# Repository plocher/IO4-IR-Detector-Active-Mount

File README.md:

# IO4-IR-Detector-Active-Mount
## License: CERN Open Hardware Licence v1.2

Mounting adapter for active IR detector remote sensor

  Designed for the Rolm RPR-220-photoreflector or equivalent IR transmitter/Detector

  * Drill a hole under the track / between the rails for the detector sensor 
  * Measure the roadbed depth and solder the sensor to the mounting plate such that the sensor does not extend up past the ties
  * solder a 4x wire harness - or a 1x4 header - to the mount, with the pins/wires facing down / away from the sensor
  * Use a screw to attach the mount under the layout

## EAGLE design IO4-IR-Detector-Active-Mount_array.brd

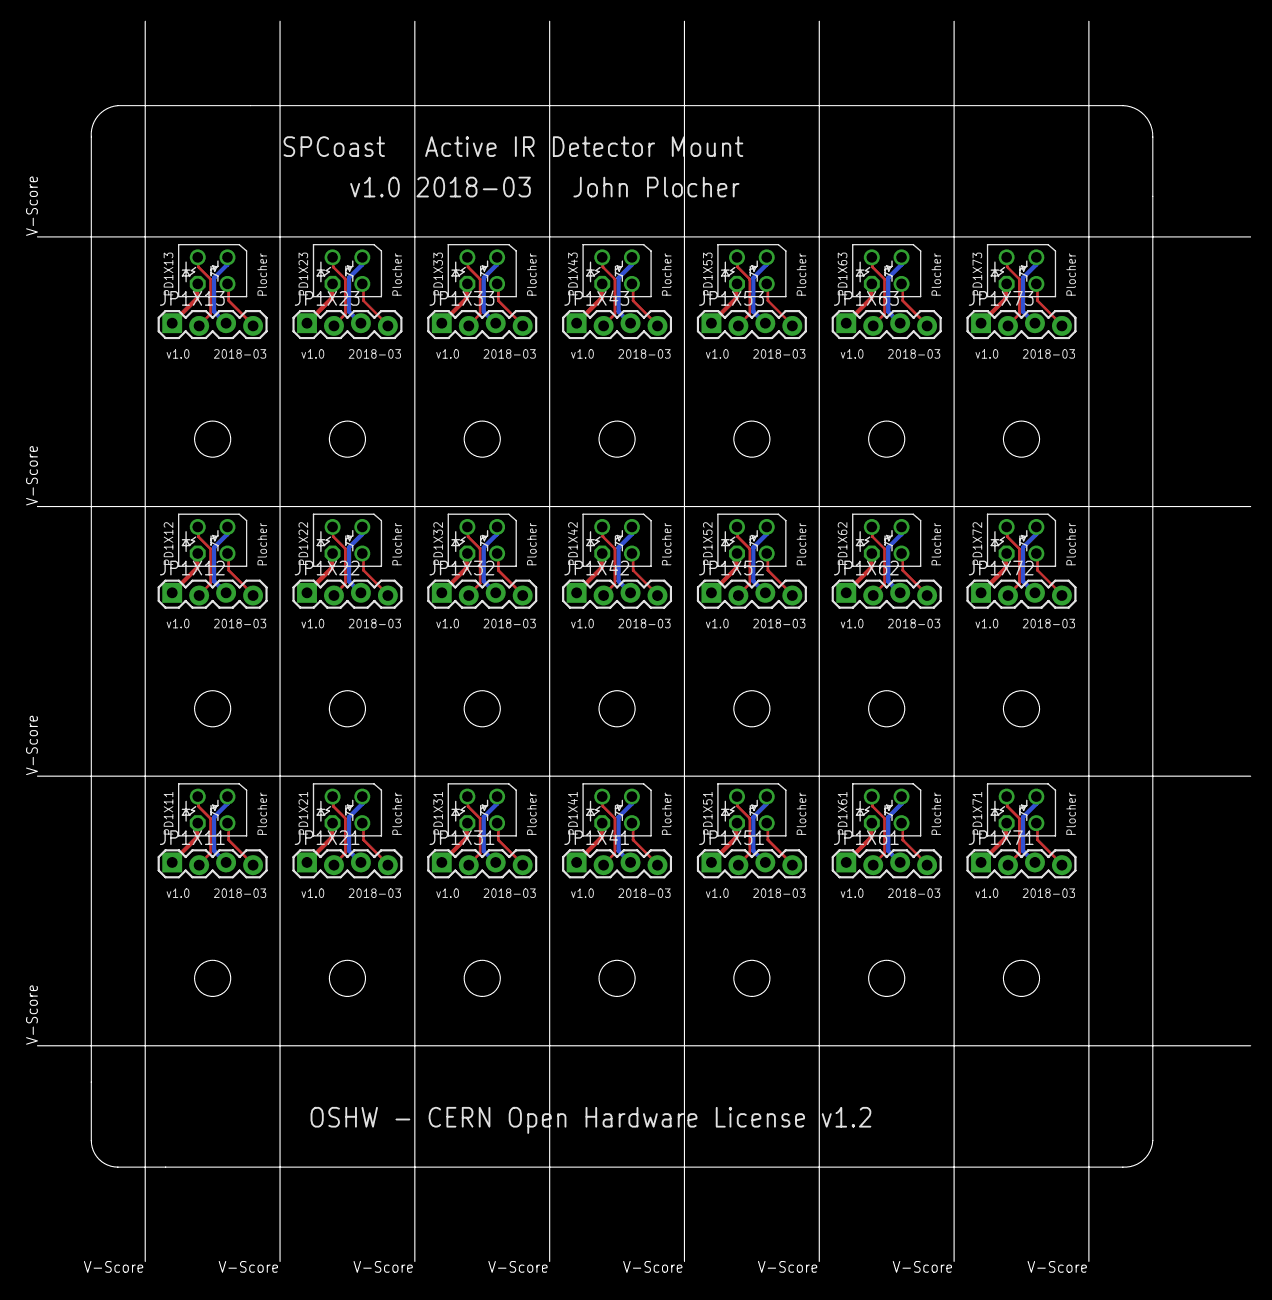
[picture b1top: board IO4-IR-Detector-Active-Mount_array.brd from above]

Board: 2 copper layers, 115.8 x 118.5 mm, 43 parts (0 on the bottom side), 84 nets.

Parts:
JP1X11, JP1X12, JP1X13, JP1X21, JP1X22, JP1X23, JP1X31, JP1X32, JP1X33, JP1X41, JP1X42, JP1X43, JP1X51, JP1X52, JP1X53, JP1X61, JP1X62, JP1X63, JP1X71, JP1X72, JP1X73: 0.100; 1X04_LOCK
PD1X1: BOARD; BOARD-SEEED10X10-NOHOLES
PD1X11, PD1X12, PD1X13, PD1X21, PD1X22, PD1X23, PD1X31, PD1X32, PD1X33, PD1X41, PD1X42, PD1X43, PD1X51, PD1X52, PD1X53, PD1X61, PD1X62, PD1X63, PD1X71, PD1X72, PD1X73: RPR220

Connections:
unnamed: JP1X11.2, PD1X11.K
unnamed: JP1X12.2, PD1X12.K
unnamed: JP1X13.2, PD1X13.K
unnamed: JP1X21.2, PD1X21.K
unnamed: JP1X22.2, PD1X22.K
unnamed: JP1X23.2, PD1X23.K
unnamed: JP1X31.2, PD1X31.K
unnamed: JP1X32.2, PD1X32.K
unnamed: JP1X33.2, PD1X33.K
unnamed: JP1X41.2, PD1X41.K
unnamed: JP1X42.2, PD1X42.K
unnamed: JP1X43.2, PD1X43.K
unnamed: JP1X51.2, PD1X51.K
unnamed: JP1X52.2, PD1X52.K
unnamed: JP1X53.2, PD1X53.K
unnamed: JP1X61.2, PD1X61.K
unnamed: JP1X62.2, PD1X62.K
unnamed: JP1X63.2, PD1X63.K
unnamed: JP1X71.2, PD1X71.K
unnamed: JP1X72.2, PD1X72.K
unnamed: JP1X73.2, PD1X73.K
unnamed: JP1X11.1, PD1X11.A
unnamed: JP1X12.1, PD1X12.A
unnamed: JP1X13.1, PD1X13.A
unnamed: JP1X21.1, PD1X21.A
unnamed: JP1X22.1, PD1X22.A
unnamed: JP1X23.1, PD1X23.A
unnamed: JP1X31.1, PD1X31.A
unnamed: JP1X32.1, PD1X32.A
unnamed: JP1X33.1, PD1X33.A
unnamed: JP1X41.1, PD1X41.A
unnamed: JP1X42.1, PD1X42.A
unnamed: JP1X43.1, PD1X43.A
unnamed: JP1X51.1, PD1X51.A
unnamed: JP1X52.1, PD1X52.A
unnamed: JP1X53.1, PD1X53.A
unnamed: JP1X61.1, PD1X61.A
unnamed: JP1X62.1, PD1X62.A
unnamed: JP1X63.1, PD1X63.A
unnamed: JP1X71.1, PD1X71.A
unnamed: JP1X72.1, PD1X72.A
unnamed: JP1X73.1, PD1X73.A
unnamed: JP1X11.4, PD1X11.COL
unnamed: JP1X12.4, PD1X12.COL
unnamed: JP1X13.4, PD1X13.COL
unnamed: JP1X21.4, PD1X21.COL
unnamed: JP1X22.4, PD1X22.COL
unnamed: JP1X23.4, PD1X23.COL
unnamed: JP1X31.4, PD1X31.COL
unnamed: JP1X32.4, PD1X32.COL
unnamed: JP1X33.4, PD1X33.COL
unnamed: JP1X41.4, PD1X41.COL
unnamed: JP1X42.4, PD1X42.COL
unnamed: JP1X43.4, PD1X43.COL
unnamed: JP1X51.4, PD1X51.COL
unnamed: JP1X52.4, PD1X52.COL
unnamed: JP1X53.4, PD1X53.COL
unnamed: JP1X61.4, PD1X61.COL
unnamed: JP1X62.4, PD1X62.COL
unnamed: JP1X63.4, PD1X63.COL
unnamed: JP1X71.4, PD1X71.COL
unnamed: JP1X72.4, PD1X72.COL
unnamed: JP1X73.4, PD1X73.COL
unnamed: JP1X11.3, PD1X11.EMIT
unnamed: JP1X12.3, PD1X12.EMIT
unnamed: JP1X13.3, PD1X13.EMIT
unnamed: JP1X21.3, PD1X21.EMIT
unnamed: JP1X22.3, PD1X22.EMIT
unnamed: JP1X23.3, PD1X23.EMIT
unnamed: JP1X31.3, PD1X31.EMIT
unnamed: JP1X32.3, PD1X32.EMIT
unnamed: JP1X33.3, PD1X33.EMIT
unnamed: JP1X41.3, PD1X41.EMIT
unnamed: JP1X42.3, PD1X42.EMIT
unnamed: JP1X43.3, PD1X43.EMIT
unnamed: JP1X51.3, PD1X51.EMIT
unnamed: JP1X52.3, PD1X52.EMIT
unnamed: JP1X53.3, PD1X53.EMIT
unnamed: JP1X61.3, PD1X61.EMIT
unnamed: JP1X62.3, PD1X62.EMIT
unnamed: JP1X63.3, PD1X63.EMIT
unnamed: JP1X71.3, PD1X71.EMIT
unnamed: JP1X72.3, PD1X72.EMIT
unnamed: JP1X73.3, PD1X73.EMIT

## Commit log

2019-11-25 markdown tweeking
2019-12-08 added graphic
2020-05-04 updated tags
2020-10-05 added values for connectors
2020-10-06 normalized values

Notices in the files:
IO4-IR-Detector-Active-Mount_array.brd:
OSHW - CERN Open Hardware License v1.2
